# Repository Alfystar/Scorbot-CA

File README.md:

------------

# Scorbot-CA (Controlli Automatici)
Progetto inizialmente portato avanti nell'ambito del corso di Controlli Automatici tenuto a Tor-Vergata nell'anno 2019
- Sviluppato da studenti del 3° Ing. Informatica
- Corso tenuto dal Professor: Daniele Carnevale

I componenti del gruppo originario erano:
- Emanuele Alfano
- Davide Antonini
- Del Papa Nicolò
- Francesco Ferrò
- Ilaria Angeloni
- Alberto Menichelli

Il progetto è attualmente portato avanti da Emanuele Alfano con la licenza [GPLv3](LICENSE "GPLv3")
<p align="center">
  
  <br>  
  
</p>

## Download/Cloning Repository
Per poter avere i sorgenti sul proprio computer, basterà usare git da terminale per clonare il Repository sulla propria macchina: 
A questo punto, compiliamo i sorgenti e installiamoli dentro /usr/local/bin
```
sudo apt install git    # Per poter scaricare i sorgenti
cd ~/Documents          # Directory di salvataggio dei sorgenti
git clone https://github.com/Alfystar/Scorbot-CA.git
```
Per vedere i sorgenti e relative guide di Compilazione andare [Qui](SW_Source/README.md)

## Documentazione
Per la realizzazione della documentazione del software si è usata la versione Comunity di Visual Paradigm.
Le classi non sono state documentate tutte al massimo dettaglio, mettendo invece enfasi sull'interconnessione, i pattern e la gerarchia delle classi presente.
er i dettagli implementativi il codice

## ScoreBoard
La scheda di controllo dello Scorbot è pensata per essere un ponte tra la meccanica del robot, e il sistema di controllo integrato all'interno di un computer Linux.

Il manuale di questo sotto sistema è trovabile [qui](1_Doc/ScorBoard_v2-MANUAL.pdf "qui").

### Eagle Board
There are 2 version of the board.
Each one have his firmware and his library.
They are drawing using EAGLE 9.4.2 Educetional.
View this project on [CADLAB.io](https://cadlab.io/project/1649). 

#####  Board V1:
In questa prima versione si sono utilizzati dei ponti H L298, e per leggere gli ACS712.
La scheda soffriva di vari problemi di connessioni tra i pin in fase di progetto, le quali sono tutte risolvibili a mano.
La scheda possiede un firmware di controllo che parla al Rapsberry Py per mezzo di una comunicazione SPI. Di questa prima vesione è stata scritta una [presentazione del progetto](1_Doc/ProjectPresentation-V1.pdf) ai fini dell'esame.

#####  Board V2:
In questa seconda scheda il cambio più evidente è nel driver motori che adesso è diventato un VNH5019, il quale ha integrato dentro una misura di corrente già scalata e non necessita di letture esterne, di questa scheda è presente anche un [**Manuale**](1_Doc/ScorBoard_v2-MANUAL.pdf "qui")., che descrive nel dettaglio i vari punti del progetto.
<p align="center">
  <i>Top Face</i>
   
  <br>
   
  <i>Bottom Face</i>
</p>

#### UART Comunication Arduino <--> Linux:
La scheda comunica con un computer mediante collegamento UART, qui è stata sviluppata una libreria per la comunicazione con un processo Linux (testata su Mint e KDE NEON, in generale ubunto based)

# QT Gui
Per controllare il Robot in maniera intuitiva si è pensato di usare un interfaccia grafica scritta in QT5, la quale permette di controllare il robot sia direttamente che per mezzo di un PID
<p align="center">
  <i>Main Window</i>
    <br>
   
  <br>
    <i>Uart Select</i>
	  <br>
   
    <br>
    <i>Setting Board Window</i>
	  <br>
   
    <br>
    <i>Free Move Window</i>
	  <br>

</p>

Per graficare i dati ricevuti è stata usata la libreria [qcustomplot](https://www.qcustomplot.com/index.php/introduction)

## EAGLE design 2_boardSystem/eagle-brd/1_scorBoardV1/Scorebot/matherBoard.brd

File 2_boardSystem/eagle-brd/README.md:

# Eagle File directory

la prima versione (1_scorBoardV1) possiede i seguenti errori:
- Il transistor di abilitazione elettrico del relè per i motori, attualmente è cortocircuitato poichè non funzionava.
La probabile causa di questo problema è che il carico è messo a emettitoere e non a colettore, rendendo il circuito adatto a un PNP e non a un NPN(che è stato progettato e comprato), in una versione successiva è necessario invertire il carico (la bobbina) con il relè.

- La piedinatura usata nell'alimentatore è errata rispetto a quella effettivamente presente, oltre ad alcuni errori che mi avevano fatto connettere 12V a 3.3V, sembra che non sia sufficente prendere la corrente da uno solo per volta di questi fili.
In una prossima versione andrebbero collegati tutti tra di loro già nella board, collegare bene i pin sbagliati e aggiungere un led di segnalazione sul filo dei 5V sempre presenti, poichè l'alimentatore anche se ha il cavo di enable(quello verde) cortocircuitato a massa, se non è assorbito un minimo di corrente cmq non si accende.
In generare riprogettare questo connettore vendendo gli infiniti schemi online e vedendo anche i fili saldati attualmente, che hanno corretto l'errore, quindi devono essere riportati sulla scheda.

- In questa scheda i 3.3V che dovevano andare al rapsberry sono stati tagliati, perchè all'inizio causavano il reset della board. Si è scoperto poi che i 3.3V erano quasi a 0 poichè cortocircuitati con 12V (evidentemente l'alimentatote andava in protezione), nella scheda successiva si può provare a collegarli quindi.

- Il Vref esterno a meno che non si prenda da meno di 1.1V è meglio levarlo potendo usare quello stabilizzato interno all'arduino

- Il connettore del Rapsberry è necessario ruotarlo di 180°, per permettere una comoda connessione con lo stesso, ovviamente così facendo bisogna rifare la strip ruotando uno dei 2 estremi, in generale controllare prima di collegare che i pin siano connessi bene

- Sempre al connettore collegare tutte le masse, i 5V e i 3.3V, così da massimizzare la potenza trasmessa

- Se si continua ad usare l'attuale relè, è necessario correggere il package della libreria da me scritta che così comè si monta all'indietro rispetto al desiderato.

- Sulla serigrafia aggiungere i sensori di corrente a quale motore fanno riferimento, per futuri debugging ad occhio

- Facilitate bypass del traslatore di livello, per leggere o annullarne la presenza (mettere una fila di pin uno per pin), e in generale spostarlo o dal lato accessibile o fuori

- Modificare la serigrafia per mettere dritto e più leggibile i loghi

Grazie per l'attenzione

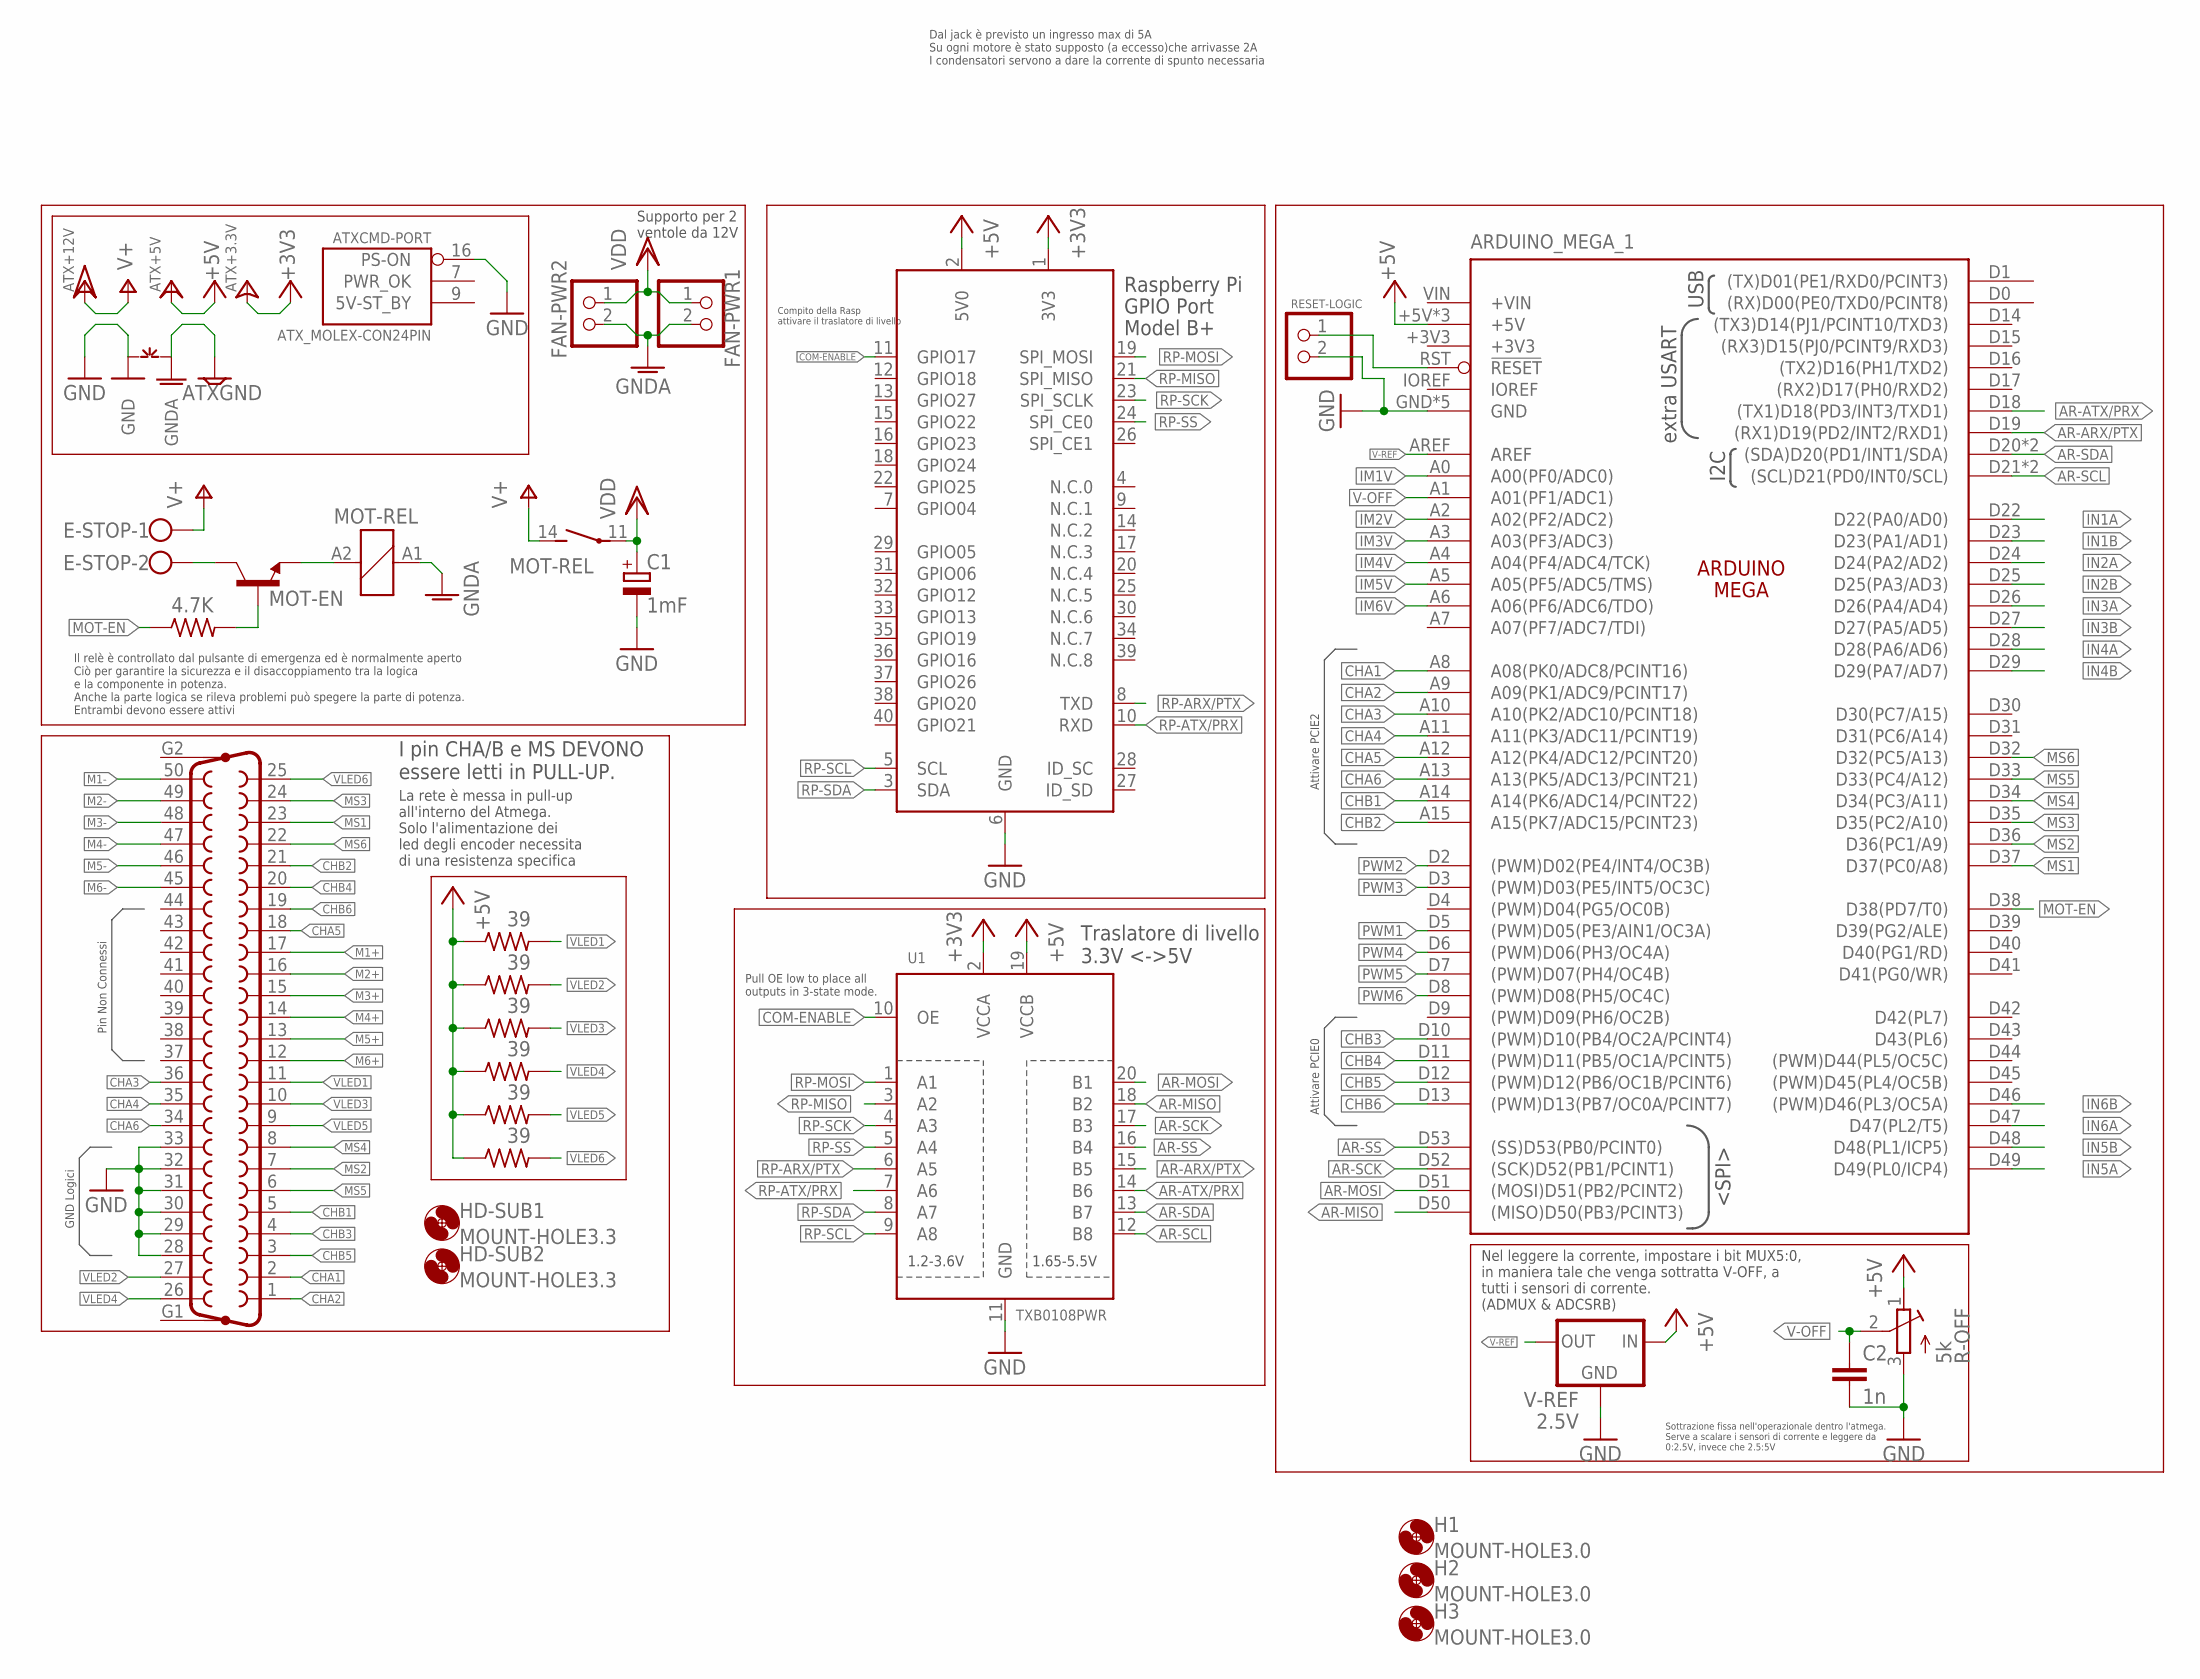
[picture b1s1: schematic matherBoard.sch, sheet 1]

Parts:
ARDUINO_MEGA_1: MEGA_ARDUINONO-HOLE; MEGA-NO-HOLE
ATX: ATX_MOLEX-CON24PIN; 5566-24
C1: 1mF; E5-13
C2: 1n; C025-024X044
D-SUB50: F50VP
E-STOP: W237-102
FAN-PWR1, FAN-PWR2: PINHD-1X2; 1X02
H1, H2, H3: MOUNT-HOLE3.0; 3,0
HD-SUB1, HD-SUB2: MOUNT-HOLE3.3; 3,3
MOT-EN: 2N5550-NPN-TO92-CBE; TO92-CBE
MOT-REL: RP530006; RP53
R1, R2, R3, R4, R5, R6: 39; 0204/5
R7: 4.7K; 0204/7
R-OFF: 5k; RTRIMT93YA
RASPBERRY-PY: RASPI_GPIO_B+_BOX
RESET-LOGIC: PINHD-1X2; 1X02
U1: TXB0108PWR; TSSOP20
V-REF: 2.5V; SOT23
~NUDEV~1: GND-GNDA1,27MM; GND-GNDA-1,27MM

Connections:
+3V3: ATX.1 (+3V3-ATX), ATX.2 (+3V3-ATX), ATX.12 (+3V3-ATX), ATX.13 (+3V3-ATX), RASPBERRY-PY.1 (3V3), U1.2 (VCCA)
+5V: ARDUINO_MEGA_1.+5V, ARDUINO_MEGA_1.+5V1 (+5V), ARDUINO_MEGA_1.+5V2 (+5V), ATX.4 (+5V-ATX), ATX.6 (+5V-ATX), ATX.21 (+5V-ATX), ATX.22 (+5V-ATX), ATX.23 (+5V-ATX), R1.1, R2.1, R3.1, R4.1, R5.1, R6.1, R-OFF.1 (E), RASPBERRY-PY.2 (5V0), U1.19 (VCCB), V-REF.3 (IN); also elsewhere on the board
AR-ARX/PTX: ARDUINO_MEGA_1.D19 ((RX1)D19(PD2/INT2/RXD1)), U1.15 (B5)
AR-ATX/PRX: ARDUINO_MEGA_1.D18 ((TX1)D18(PD3/INT3/TXD1)), U1.14 (B6)
AR-MISO: ARDUINO_MEGA_1.D50 ((MISO)D50(PB3/PCINT3)), U1.18 (B2)
AR-MOSI: ARDUINO_MEGA_1.D51 ((MOSI)D51(PB2/PCINT2)), U1.20 (B1)
AR-SCK: ARDUINO_MEGA_1.D52 ((SCK)D52(PB1/PCINT1)), U1.17 (B3)
AR-SCL: ARDUINO_MEGA_1.D21 ((SCL)D21(PD0/INT0/SCL)), ARDUINO_MEGA_1.SCL1 ((SCL)D21(PD0/INT0/SCL)), U1.12 (B8)
AR-SDA: ARDUINO_MEGA_1.D20 ((SDA)D20(PD1/INT1/SDA)), ARDUINO_MEGA_1.SDA1 ((SDA)D20(PD1/INT1/SDA)), U1.13 (B7)
AR-SS: ARDUINO_MEGA_1.D53 ((SS)D53(PB0/PCINT0)), U1.16 (B4)
CHA1: ARDUINO_MEGA_1.A8 (A08(PK0/ADC8/PCINT16)), D-SUB50.2
CHA2: ARDUINO_MEGA_1.A9 (A09(PK1/ADC9/PCINT17)), D-SUB50.1
CHA3: ARDUINO_MEGA_1.A10 (A10(PK2/ADC10/PCINT18)), D-SUB50.36
CHA4: ARDUINO_MEGA_1.A11 (A11(PK3/ADC11/PCINT19)), D-SUB50.35
CHA5: ARDUINO_MEGA_1.A12 (A12(PK4/ADC12/PCINT20)), D-SUB50.18
CHA6: ARDUINO_MEGA_1.A13 (A13(PK5/ADC13/PCINT21)), D-SUB50.34
CHB1: ARDUINO_MEGA_1.A14 (A14(PK6/ADC14/PCINT22)), D-SUB50.5
CHB2: ARDUINO_MEGA_1.A15 (A15(PK7/ADC15/PCINT23)), D-SUB50.21
CHB3: ARDUINO_MEGA_1.D10 ((PWM)D10(PB4/OC2A/PCINT4)), D-SUB50.4
CHB4: ARDUINO_MEGA_1.D11 ((PWM)D11(PB5/OC1A/PCINT5)), D-SUB50.20
CHB5: ARDUINO_MEGA_1.D12 ((PWM)D12(PB6/OC1B/PCINT6)), D-SUB50.3
CHB6: ARDUINO_MEGA_1.D13 ((PWM)D13(PB7/OC0A/PCINT7)), D-SUB50.19
COM-ENABLE: RASPBERRY-PY.11 (GPIO17), U1.10 (OE)
GND: ARDUINO_MEGA_1.GND, ARDUINO_MEGA_1.GND1 (GND), ARDUINO_MEGA_1.GND2 (GND), ARDUINO_MEGA_1.GND3 (GND), ARDUINO_MEGA_1.GND4 (GND), ATX.16 (PS-ON), C1.-, C2.2, D-SUB50.28, D-SUB50.29, D-SUB50.30, D-SUB50.31, D-SUB50.32, D-SUB50.33, R-OFF.3 (A), RASPBERRY-PY.6 (GND), RESET-LOGIC.2, U1.11 (GND), V-REF.1 (GND), ~NUDEV~1.GND; also elsewhere on the board
GNDA: ATX.3 (GND-ATX), ATX.5 (GND-ATX), ATX.8 (GND-ATX), ATX.15 (GND-ATX), ATX.17 (GND-ATX), ATX.18 (GND-ATX), ATX.19 (GND-ATX), ATX.24 (GND-ATX), FAN-PWR1.2, FAN-PWR2.2, MOT-REL.A1 (1), ~NUDEV~1.GNDA; also elsewhere on the board
IM1V: ARDUINO_MEGA_1.A0 (A00(PF0/ADC0)); also elsewhere on the board
IM2V: ARDUINO_MEGA_1.A2 (A02(PF2/ADC2)); also elsewhere on the board
IM3V: ARDUINO_MEGA_1.A3 (A03(PF3/ADC3)); also elsewhere on the board
IM4V: ARDUINO_MEGA_1.A4 (A04(PF4/ADC4/TCK)); also elsewhere on the board
IM5V: ARDUINO_MEGA_1.A5 (A05(PF5/ADC5/TMS)); also elsewhere on the board
IM6V: ARDUINO_MEGA_1.A6 (A06(PF6/ADC6/TDO)); also elsewhere on the board
IN1A: ARDUINO_MEGA_1.D22 (D22(PA0/AD0)); also elsewhere on the board
IN1B: ARDUINO_MEGA_1.D23 (D23(PA1/AD1)); also elsewhere on the board
IN2A: ARDUINO_MEGA_1.D24 (D24(PA2/AD2)); also elsewhere on the board
IN2B: ARDUINO_MEGA_1.D25 (D25(PA3/AD3)); also elsewhere on the board
IN3A: ARDUINO_MEGA_1.D26 (D26(PA4/AD4)); also elsewhere on the board
IN3B: ARDUINO_MEGA_1.D27 (D27(PA5/AD5)); also elsewhere on the board
IN4A: ARDUINO_MEGA_1.D28 (D28(PA6/AD6)); also elsewhere on the board
IN4B: ARDUINO_MEGA_1.D29 (D29(PA7/AD7)); also elsewhere on the board
IN5A: ARDUINO_MEGA_1.D49 (D49(PL0/ICP4)); also elsewhere on the board
IN5B: ARDUINO_MEGA_1.D48 (D48(PL1/ICP5)); also elsewhere on the board
IN6A: ARDUINO_MEGA_1.D47 (D47(PL2/T5)); also elsewhere on the board
IN6B: ARDUINO_MEGA_1.D46 ((PWM)D46(PL3/OC5A)); also elsewhere on the board
M1+: D-SUB50.17; also elsewhere on the board
M1-: D-SUB50.50; also elsewhere on the board
M2+: D-SUB50.16; also elsewhere on the board
M2-: D-SUB50.49; also elsewhere on the board
M3+: D-SUB50.15; also elsewhere on the board
M3-: D-SUB50.48; also elsewhere on the board
M4+: D-SUB50.14; also elsewhere on the board
M4-: D-SUB50.47; also elsewhere on the board
M5+: D-SUB50.13; also elsewhere on the board
M5-: D-SUB50.46; also elsewhere on the board
M6+: D-SUB50.12; also elsewhere on the board
M6-: D-SUB50.45; also elsewhere on the board
MOT-EN: ARDUINO_MEGA_1.D38 (D38(PD7/T0)), R7.1
MS1: ARDUINO_MEGA_1.D37 (D37(PC0/A8)), D-SUB50.23
MS2: ARDUINO_MEGA_1.D36 (D36(PC1/A9)), D-SUB50.7
MS3: ARDUINO_MEGA_1.D35 (D35(PC2/A10)), D-SUB50.24
MS4: ARDUINO_MEGA_1.D34 (D34(PC3/A11)), D-SUB50.8
MS5: ARDUINO_MEGA_1.D33 (D33(PC4/A12)), D-SUB50.6
MS6: ARDUINO_MEGA_1.D32 (D32(PC5/A13)), D-SUB50.22
unnamed: E-STOP.2, MOT-EN.C
unnamed: MOT-EN.B, R7.2
unnamed: MOT-EN.E, MOT-REL.A2 (2)
unnamed: ARDUINO_MEGA_1.RST (!RESET), RESET-LOGIC.1
PWM1: ARDUINO_MEGA_1.D5 ((PWM)D05(PE3/AIN1/OC3A)); also elsewhere on the board
PWM2: ARDUINO_MEGA_1.D2 ((PWM)D02(PE4/INT4/OC3B)); also elsewhere on the board
PWM3: ARDUINO_MEGA_1.D3 ((PWM)D03(PE5/INT5/OC3C)); also elsewhere on the board
PWM4: ARDUINO_MEGA_1.D6 ((PWM)D06(PH3/OC4A)); also elsewhere on the board
PWM5: ARDUINO_MEGA_1.D7 ((PWM)D07(PH4/OC4B)); also elsewhere on the board
PWM6: ARDUINO_MEGA_1.D8 ((PWM)D08(PH5/OC4C)); also elsewhere on the board
RP-ARX/PTX: RASPBERRY-PY.8 (TXD), U1.6 (A5)
RP-ATX/PRX: RASPBERRY-PY.10 (RXD), U1.7 (A6)
RP-MISO: RASPBERRY-PY.21 (SPI_MISO), U1.3 (A2)
RP-MOSI: RASPBERRY-PY.19 (SPI_MOSI), U1.1 (A1)
RP-SCK: RASPBERRY-PY.23 (SPI_SCLK), U1.4 (A3)
RP-SCL: RASPBERRY-PY.5 (SCL), U1.9 (A8)
RP-SDA: RASPBERRY-PY.3 (SDA), U1.8 (A7)
RP-SS: RASPBERRY-PY.24 (SPI_CE0), U1.5 (A4)
V+: ATX.10 (VCC/2), ATX.11 (VCC/2), E-STOP.1, MOT-REL.14 (S)
V-OFF: ARDUINO_MEGA_1.A1 (A01(PF1/ADC1)), C2.1, R-OFF.2 (S)
V-REF: ARDUINO_MEGA_1.AREF, V-REF.2 (OUT)
VDD: C1.+, FAN-PWR1.1, FAN-PWR2.1, MOT-REL.11; also elsewhere on the board
VLED1: D-SUB50.11, R1.2
VLED2: D-SUB50.27, R2.2
VLED3: D-SUB50.10, R3.2
VLED4: D-SUB50.26, R4.2
VLED5: D-SUB50.9, R5.2
VLED6: D-SUB50.25, R6.2

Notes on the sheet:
GND Logici
Dal jack è previsto un ingresso max di 5A Su ogni motore è stato supposto (a eccesso)che arrivasse 2A I condensatori servono a dare la corrente di spunto necessaria
Il relè è controllato dal pulsante di emergenza ed è normalmente aperto Ciò per garantire la sicurezza e il disaccoppiamento tra la logica e la componente in potenza. Anche la parte logica se rileva problemi può spegere la parte di potenza. Entrambi devono essere attivi
La rete è messa in pull-up all'interno del Atmega. Solo l'alimentazione dei led degli encoder necessita di una resistenza specifica
Pin Non Connessi
Pull OE low to place all outputs in 3-state mode.
Attivare PCIE2
Attivare PCIE0
I pin CHA/B e MS DEVONO essere letti in PULL-UP.
Sottrazione fissa nell'operazionale dentro l'atmega. Serve a scalare i sensori di corrente e leggere da 0:2.5V, invece che 2.5:5V
Nel leggere la corrente, impostare i bit MUX5:0, in maniera tale che venga sottratta V-OFF, a tutti i sensori di corrente. (ADMUX & ADCSRB)
Supporto per 2 ventole da 12V
Traslatore di livello 3.3V <->5V
Compito della Rasp attivare il traslatore di livello

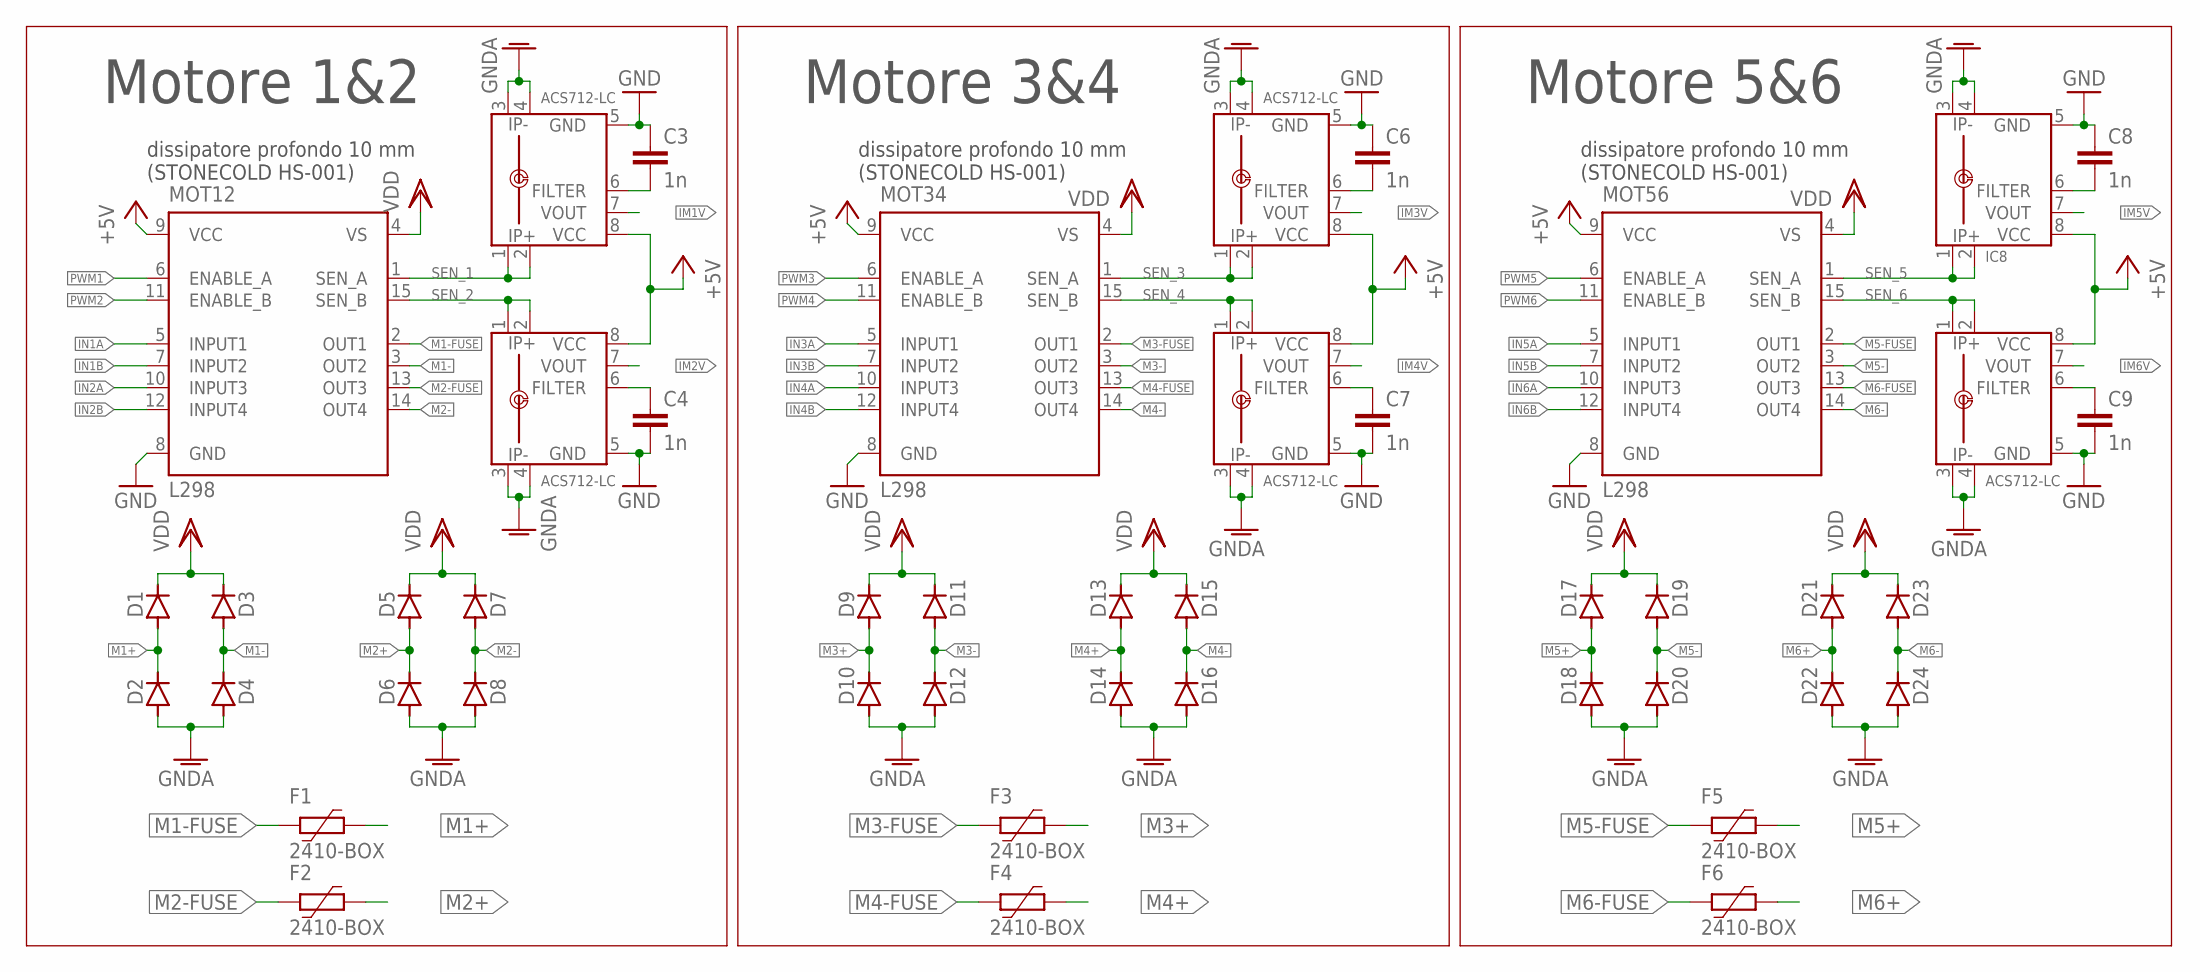
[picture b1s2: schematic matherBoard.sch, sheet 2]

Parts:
C3, C4, C6, C7, C8, C9: 1n; C025-024X044
D1, D2, D3, D4, D5, D6, D7, D8, D9, D10, D11, D12, D13, D14, D15, D16, D17, D18, D19, D20, D21, D22, D23, D24: ES2D; SMB
F1, F2, F3, F4, F5, F6: 2410-BOX; BELFUSE0679-3000-12
IC2, IC3, IC5, IC6, IC8, IC9: ACS712-LC; SOIC8
MOT12, MOT34, MOT56: L298; MULTIWATT-15

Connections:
+5V: IC2.8 (VCC), IC3.8 (VCC), IC5.8 (VCC), IC6.8 (VCC), IC8.8 (VCC), IC9.8 (VCC), MOT12.9 (VCC), MOT34.9 (VCC), MOT56.9 (VCC); also elsewhere on the board
GND: C3.1, C4.2, C6.1, C7.2, C8.1, C9.2, IC2.5 (GND), IC3.5 (GND), IC5.5 (GND), IC6.5 (GND), IC8.5 (GND), IC9.5 (GND), MOT12.8 (GND), MOT34.8 (GND), MOT56.8 (GND); also elsewhere on the board
GNDA: D2.A, D4.A, D6.A, D8.A, D10.A, D12.A, D14.A, D16.A, D18.A, D20.A, D22.A, D24.A, IC2.3 (IP-), IC2.4 (IP-1), IC3.3 (IP-), IC3.4 (IP-1), IC5.3 (IP-), IC5.4 (IP-1), IC6.3 (IP-), IC6.4 (IP-1), IC8.3 (IP-), IC8.4 (IP-1), IC9.3 (IP-), IC9.4 (IP-1); also elsewhere on the board
IM1V: IC2.7 (VOUT); also elsewhere on the board
IM2V: IC3.7 (VOUT); also elsewhere on the board
IM3V: IC5.7 (VOUT); also elsewhere on the board
IM4V: IC6.7 (VOUT); also elsewhere on the board
IM5V: IC8.7 (VOUT); also elsewhere on the board
IM6V: IC9.7 (VOUT); also elsewhere on the board
IN1A: MOT12.5 (INPUT1); also elsewhere on the board
IN1B: MOT12.7 (INPUT2); also elsewhere on the board
IN2A: MOT12.10 (INPUT3); also elsewhere on the board
IN2B: MOT12.12 (INPUT4); also elsewhere on the board
IN3A: MOT34.5 (INPUT1); also elsewhere on the board
IN3B: MOT34.7 (INPUT2); also elsewhere on the board
IN4A: MOT34.10 (INPUT3); also elsewhere on the board
IN4B: MOT34.12 (INPUT4); also elsewhere on the board
IN5A: MOT56.5 (INPUT1); also elsewhere on the board
IN5B: MOT56.7 (INPUT2); also elsewhere on the board
IN6A: MOT56.10 (INPUT3); also elsewhere on the board
IN6B: MOT56.12 (INPUT4); also elsewhere on the board
M1+: D1.A, D2.C, F1.1; also elsewhere on the board
M1-: D3.A, D4.C, MOT12.3 (OUT2); also elsewhere on the board
M1-FUSE: F1.2, MOT12.2 (OUT1)
M2+: D5.A, D6.C, F2.1; also elsewhere on the board
M2-: D7.A, D8.C, MOT12.14 (OUT4); also elsewhere on the board
M2-FUSE: F2.2, MOT12.13 (OUT3)
M3+: D9.A, D10.C, F3.1; also elsewhere on the board
M3-: D11.A, D12.C, MOT34.3 (OUT2); also elsewhere on the board
M3-FUSE: F3.2, MOT34.2 (OUT1)
M4+: D13.A, D14.C, F4.1; also elsewhere on the board
M4-: D15.A, D16.C, MOT34.14 (OUT4); also elsewhere on the board
M4-FUSE: F4.2, MOT34.13 (OUT3)
M5+: D17.A, D18.C, F5.1; also elsewhere on the board
M5-: D19.A, D20.C, MOT56.3 (OUT2); also elsewhere on the board
M5-FUSE: F5.2, MOT56.2 (OUT1)
M6+: D21.A, D22.C, F6.1; also elsewhere on the board
M6-: D23.A, D24.C, MOT56.14 (OUT4); also elsewhere on the board
M6-FUSE: F6.2, MOT56.13 (OUT3)
unnamed: C3.2, IC2.6 (FILTER)
unnamed: C4.1, IC3.6 (FILTER)
unnamed: C6.2, IC5.6 (FILTER)
unnamed: C7.1, IC6.6 (FILTER)
unnamed: C8.2, IC8.6 (FILTER)
unnamed: C9.1, IC9.6 (FILTER)
PWM1: MOT12.6 (ENABLE_A); also elsewhere on the board
PWM2: MOT12.11 (ENABLE_B); also elsewhere on the board
PWM3: MOT34.6 (ENABLE_A); also elsewhere on the board
PWM4: MOT34.11 (ENABLE_B); also elsewhere on the board
PWM5: MOT56.6 (ENABLE_A); also elsewhere on the board
PWM6: MOT56.11 (ENABLE_B); also elsewhere on the board
SEN_1: IC2.1 (IP+), IC2.2 (IP+1), MOT12.1 (SEN_A)
SEN_2: IC3.1 (IP+), IC3.2 (IP+1), MOT12.15 (SEN_B)
SEN_3: IC5.1 (IP+), IC5.2 (IP+1), MOT34.1 (SEN_A)
SEN_4: IC6.1 (IP+), IC6.2 (IP+1), MOT34.15 (SEN_B)
SEN_5: IC8.1 (IP+), IC8.2 (IP+1), MOT56.1 (SEN_A)
SEN_6: IC9.1 (IP+), IC9.2 (IP+1), MOT56.15 (SEN_B)
VDD: D1.C, D3.C, D5.C, D7.C, D9.C, D11.C, D13.C, D15.C, D17.C, D19.C, D21.C, D23.C, MOT12.4 (VS), MOT34.4 (VS), MOT56.4 (VS); also elsewhere on the board

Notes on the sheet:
dissipatore profondo 10 mm (STONECOLD HS-001)
Motore 1&2
Motore 3&4
Motore 5&6

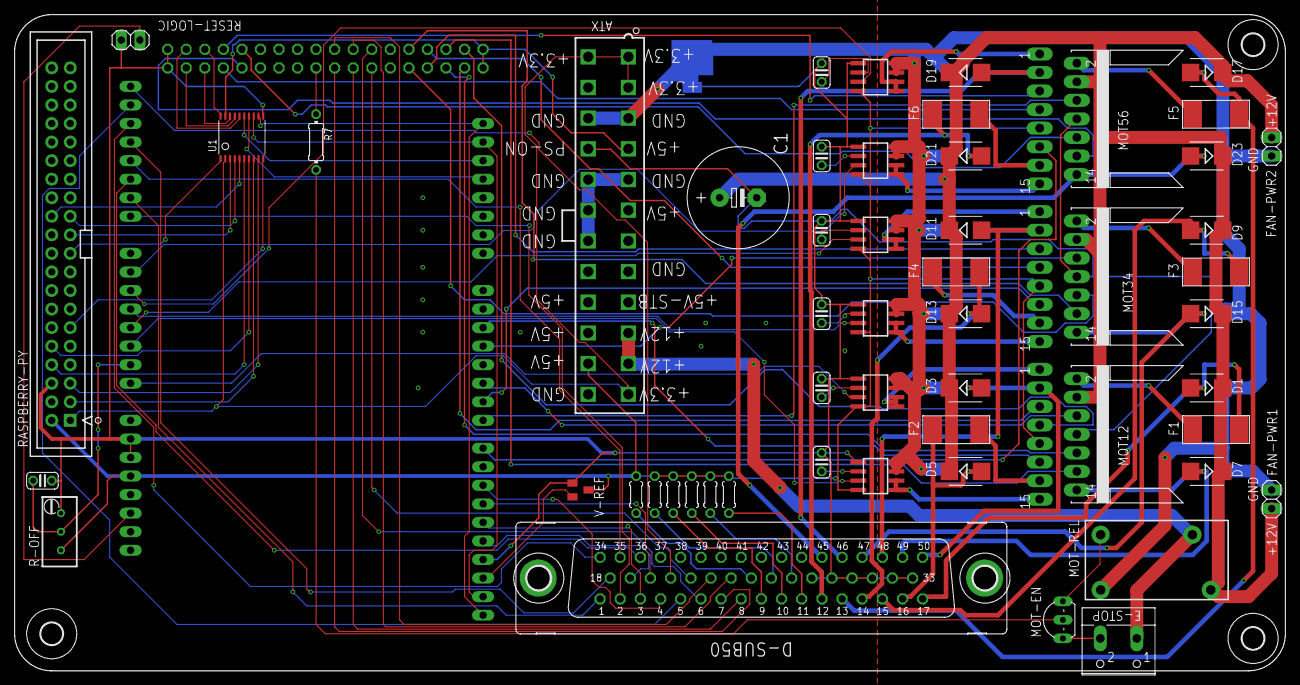
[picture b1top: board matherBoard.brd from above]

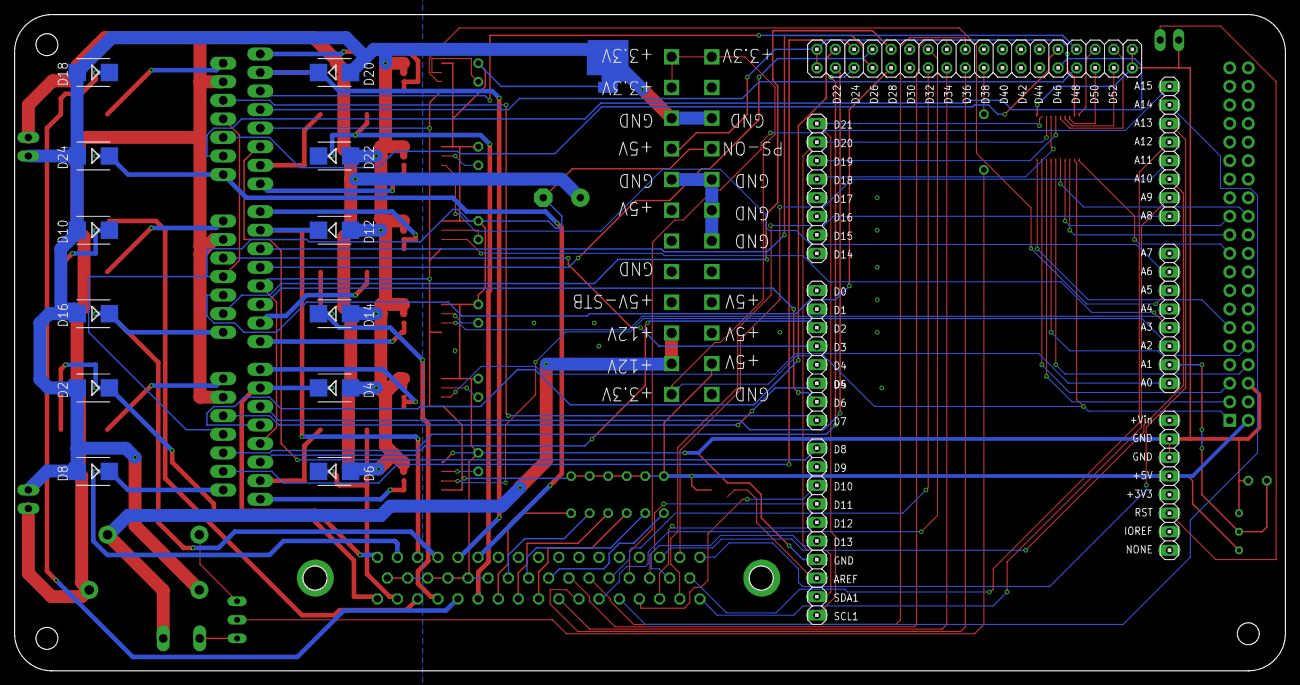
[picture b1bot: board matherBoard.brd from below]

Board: 2 copper layers, 174.0 x 89.8 mm, 73 parts (14 on the bottom side), 108 nets.

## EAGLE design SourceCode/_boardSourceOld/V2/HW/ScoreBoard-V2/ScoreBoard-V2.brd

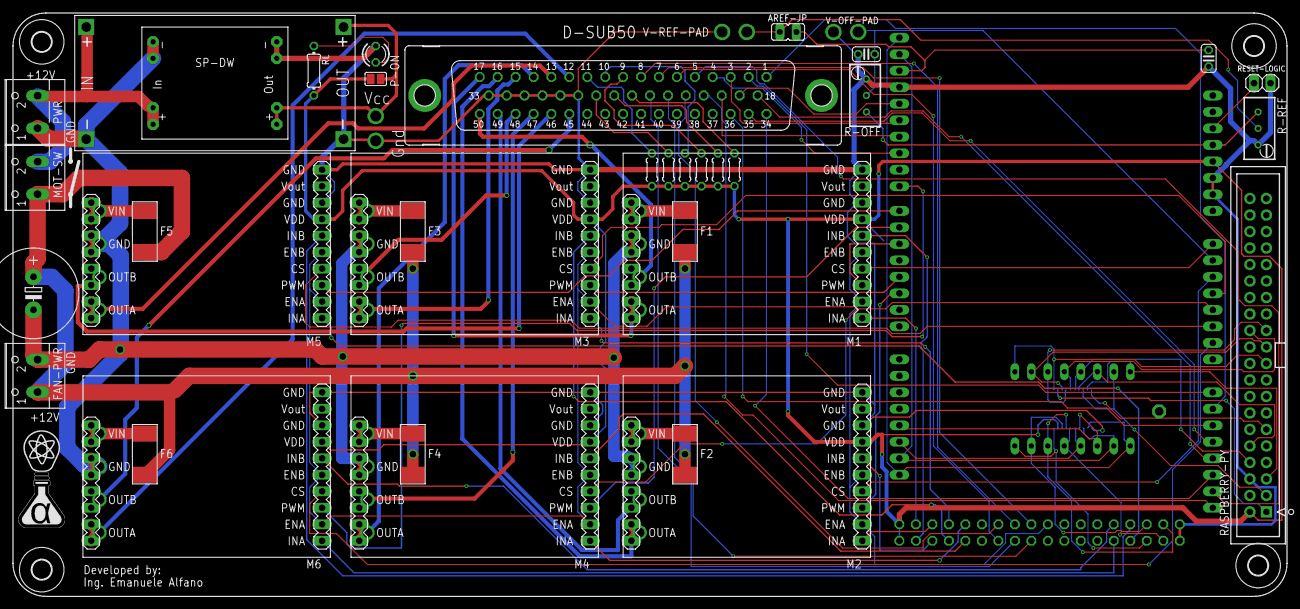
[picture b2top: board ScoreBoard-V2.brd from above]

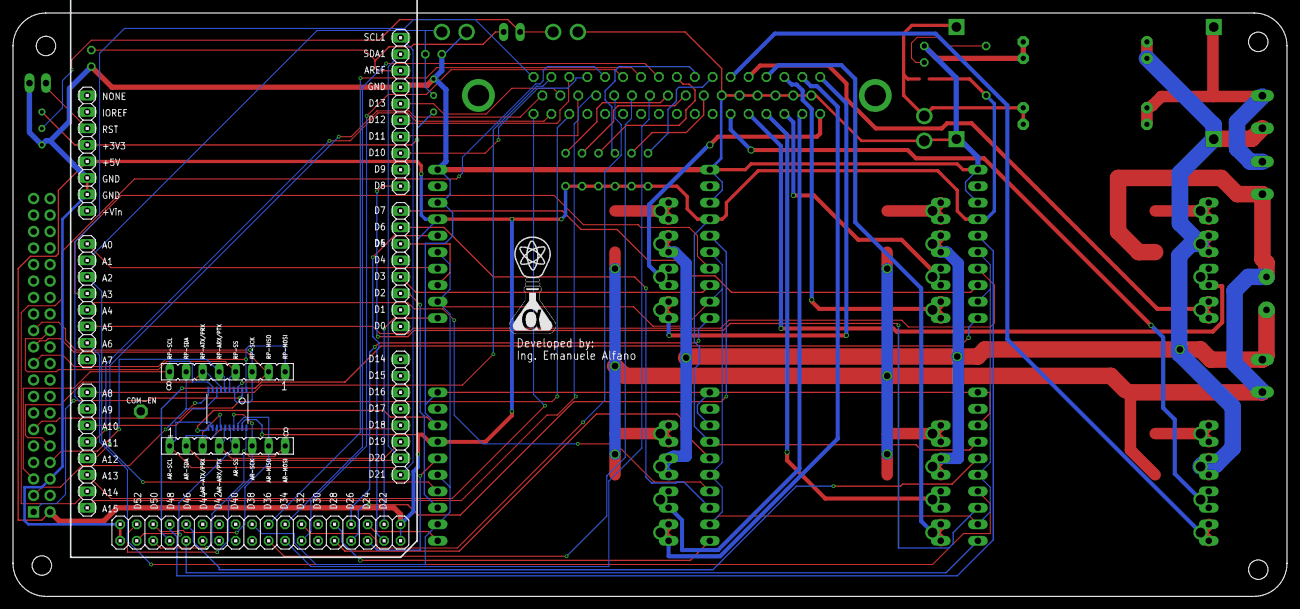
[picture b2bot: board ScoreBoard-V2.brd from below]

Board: 2 copper layers, 196.2 x 89.8 mm, 48 parts (5 on the bottom side), 97 nets.

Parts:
ARDUINO_MEGA_1: MEGA_ARDUINONO-HOLE; MEGA-NO-HOLE
AREF-JP: JP1
C1: 1mF; E5-13
C2, C3: 1n; C025-024X044
COM-EN: PTR1PAD1-13; P1-13
D-SUB50: F50VP
F1, F2, F3, F4, F5, F6: 2410-BOX; BELFUSE0679-3000-12
FAN-PWR: W237-102
H1, H2, H3, H4: MOUNT-HOLE3.0; 3,0
M1, M2, M3, M4, M5, M6: VNH5019
MOT-SW: W237-102
P-ON: LED3MM
PWR: W237-102
R1, R2, R3, R4, R5, R6: 39; 0204/5
R-OFF: 5k; RTRIMT93YA
R-REF: 5k; RTRIMT93YA
RASPBERRY-PY: RASPI_GPIO_B+_BOX
RESET-LOGIC: 1X02
RL: 330; 0204/7
SJ2: SJ
SP-DW: DC/DC-STEP-DOWNGLOB; DC/DC-STEP-DOWN-UNIVERSAL
SV1, SV2: FE08
U1: TXB0108; TSSOP20
U$2, U$3: ALFY_15MM
V-OFF-PAD: TP2P2-38-17; P2-38-17
V-REF-PAD: TP2P2-38-17; P2-38-17
VTEST-: TP2P2-38-17; P2-38-17

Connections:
3.3V-ARD: ARDUINO_MEGA_1.+3V3, R-OFF.1, R-REF.1
+3V3: RASPBERRY-PY.1, U1.2
+5V: ARDUINO_MEGA_1.+5V, ARDUINO_MEGA_1.+5V1, ARDUINO_MEGA_1.+5V2, M1.VDD, M2.VDD, M3.VDD, M4.VDD, M5.VDD, M6.VDD, R1.1, R2.1, R3.1, R4.1, R5.1, R6.1, RASPBERRY-PY.2, RL.2, SJ2.2, U1.19
AR-ARX/PTX: ARDUINO_MEGA_1.D19, SV2.4, U1.15
AR-ATX/PRX: ARDUINO_MEGA_1.D18, SV2.3, U1.14
AR-MISO: ARDUINO_MEGA_1.D50, SV2.7, U1.18
AR-MOSI: ARDUINO_MEGA_1.D51, SV2.8, U1.20
AR-SCK: ARDUINO_MEGA_1.D52, SV2.6, U1.17
AR-SCL: ARDUINO_MEGA_1.D21, ARDUINO_MEGA_1.SCL1, SV2.1, U1.12
AR-SDA: ARDUINO_MEGA_1.D20, ARDUINO_MEGA_1.SDA1, SV2.2, U1.13
AR-SS: ARDUINO_MEGA_1.D53, SV2.5, U1.16
CHA1: ARDUINO_MEGA_1.A8, D-SUB50.2
CHA2: ARDUINO_MEGA_1.A9, D-SUB50.1
CHA3: ARDUINO_MEGA_1.A10, D-SUB50.36
CHA4: ARDUINO_MEGA_1.A11, D-SUB50.35
CHA5: ARDUINO_MEGA_1.A12, D-SUB50.18
CHA6: ARDUINO_MEGA_1.A13, D-SUB50.34
CHB1: ARDUINO_MEGA_1.A14, D-SUB50.5
CHB2: ARDUINO_MEGA_1.A15, D-SUB50.21
CHB3: ARDUINO_MEGA_1.D10, D-SUB50.4
CHB4: ARDUINO_MEGA_1.D11, D-SUB50.20
CHB5: ARDUINO_MEGA_1.D12, D-SUB50.3
CHB6: ARDUINO_MEGA_1.D13, D-SUB50.19
COM-ENABLE: COM-EN.TP, RASPBERRY-PY.11, U1.10
GND: ARDUINO_MEGA_1.GND, ARDUINO_MEGA_1.GND1, ARDUINO_MEGA_1.GND2, ARDUINO_MEGA_1.GND3, ARDUINO_MEGA_1.GND4, C2.2, C3.2, D-SUB50.28, D-SUB50.29, D-SUB50.30, D-SUB50.31, D-SUB50.32, D-SUB50.33, M1.GND, M1.GND1, M2.GND, M2.GND1, M3.GND, M3.GND1, M4.GND, M4.GND1, M5.GND, M5.GND1, M6.GND, M6.GND1, P-ON.K, R-OFF.3, R-REF.3, RASPBERRY-PY.6, RESET-LOGIC.2, SP-DW.OUT-, SP-DW.OUT-1, SP-DW.OUT-2, U1.11, V-OFF-PAD.TP-2, V-REF-PAD.TP-2, VTEST-.TP-2
GNDA: C1.-, FAN-PWR.2, M1.GND-P1, M1.GND-P2, M1.GND-P3, M2.GND-P1, M2.GND-P2, M2.GND-P3, M3.GND-P1, M3.GND-P2, M3.GND-P3, M4.GND-P1, M4.GND-P2, M4.GND-P3, M5.GND-P1, M5.GND-P2, M5.GND-P3, M6.GND-P1, M6.GND-P2, M6.GND-P3, PWR.1, SP-DW.IN-, SP-DW.IN-1, SP-DW.IN-2
IM1V: ARDUINO_MEGA_1.A0, M1.CS
IM2V: ARDUINO_MEGA_1.A2, M2.CS
IM3V: ARDUINO_MEGA_1.A3, M3.CS
IM4V: ARDUINO_MEGA_1.A4, M4.CS
IM5V: ARDUINO_MEGA_1.A5, M5.CS
IM6V: ARDUINO_MEGA_1.A6, M6.CS
IN1A: ARDUINO_MEGA_1.D22, M1.INA
IN1B: ARDUINO_MEGA_1.D23, M1.INB
IN2A: ARDUINO_MEGA_1.D24, M2.INA
IN2B: ARDUINO_MEGA_1.D25, M2.INB
IN3A: ARDUINO_MEGA_1.D26, M3.INA
IN3B: ARDUINO_MEGA_1.D27, M3.INB
IN4A: ARDUINO_MEGA_1.D28, M4.INA
IN4B: ARDUINO_MEGA_1.D29, M4.INB
IN5A: ARDUINO_MEGA_1.D49, M5.INA
IN5B: ARDUINO_MEGA_1.D48, M5.INB
IN6A: ARDUINO_MEGA_1.D47, M6.INA
IN6B: ARDUINO_MEGA_1.D46, M6.INB
M1+: D-SUB50.17, M1.OUTA, M1.OUTA2, M1.OUTA3
M1-: D-SUB50.50, M1.OUTB, M1.OUTB1, M1.OUTB3
M1-FUSE: F1.1, M1.VIN0, M1.VIN1, M1.VIN2
M2+: D-SUB50.16, M2.OUTA, M2.OUTA2, M2.OUTA3
M2-: D-SUB50.49, M2.OUTB, M2.OUTB1, M2.OUTB3
M2-FUSE: F2.1, M2.VIN0, M2.VIN1, M2.VIN2
M3+: D-SUB50.15, M3.OUTA, M3.OUTA2, M3.OUTA3
M3-: D-SUB50.48, M3.OUTB, M3.OUTB1, M3.OUTB3
M3-FUSE: F3.1, M3.VIN0, M3.VIN1, M3.VIN2
M4+: D-SUB50.14, M4.OUTA, M4.OUTA2, M4.OUTA3
M4-: D-SUB50.47, M4.OUTB, M4.OUTB1, M4.OUTB3
M4-FUSE: F4.1, M4.VIN0, M4.VIN1, M4.VIN2
M5+: D-SUB50.13, M5.OUTA, M5.OUTA2, M5.OUTA3
M5-: D-SUB50.46, M5.OUTB, M5.OUTB1, M5.OUTB3
M5-FUSE: F5.1, M5.VIN0, M5.VIN1, M5.VIN2
M6+: D-SUB50.12, M6.OUTA, M6.OUTA2, M6.OUTA3
M6-: D-SUB50.45, M6.OUTB, M6.OUTB1, M6.OUTB3
M6-FUSE: F6.1, M6.VIN0, M6.VIN1, M6.VIN2
MOT-EN: ARDUINO_MEGA_1.D38, M1.ENA, M1.ENB, M2.ENA, M2.ENB, M3.ENA, M3.ENB, M4.ENA, M4.ENB, M5.ENA, M5.ENB, M6.ENA, M6.ENB
MS1: ARDUINO_MEGA_1.D37, D-SUB50.23
MS2: ARDUINO_MEGA_1.D36, D-SUB50.7
MS3: ARDUINO_MEGA_1.D35, D-SUB50.24
MS4: ARDUINO_MEGA_1.D34, D-SUB50.8
MS5: ARDUINO_MEGA_1.D33, D-SUB50.6
MS6: ARDUINO_MEGA_1.D32, D-SUB50.22
unnamed: P-ON.A, RL.1
unnamed: SJ2.1, SP-DW.OUT+, SP-DW.OUT+1, SP-DW.OUT+2, VTEST-.TP-1
unnamed: ARDUINO_MEGA_1.RST, RESET-LOGIC.1
PWM1: ARDUINO_MEGA_1.D5, M1.PWM
PWM2: ARDUINO_MEGA_1.D2, M2.PWM
PWM3: ARDUINO_MEGA_1.D3, M3.PWM
PWM4: ARDUINO_MEGA_1.D6, M4.PWM
PWM5: ARDUINO_MEGA_1.D7, M5.PWM
PWM6: ARDUINO_MEGA_1.D8, M6.PWM
RP-ARX/PTX: RASPBERRY-PY.8, SV1.5, U1.6
RP-ATX/PRX: RASPBERRY-PY.10, SV1.6, U1.7
RP-MISO: RASPBERRY-PY.21, SV1.2, U1.3
RP-MOSI: RASPBERRY-PY.19, SV1.1, U1.1
RP-SCK: RASPBERRY-PY.23, SV1.3, U1.4
RP-SCL: RASPBERRY-PY.5, SV1.8, U1.9
RP-SDA: RASPBERRY-PY.3, SV1.7, U1.8
RP-SS: RASPBERRY-PY.24, SV1.4, U1.5
V+: MOT-SW.2, PWR.2, SP-DW.IN+, SP-DW.IN+1, SP-DW.IN+2
V-OFF: ARDUINO_MEGA_1.A1, C3.1, R-OFF.2, V-OFF-PAD.TP-1
V-REF: ARDUINO_MEGA_1.AREF, AREF-JP.1, C2.1
V-REF-TRIMM: AREF-JP.2, R-REF.2, V-REF-PAD.TP-1
VDD: C1.+, F1.2, F2.2, F3.2, F4.2, F5.2, F6.2, FAN-PWR.1, MOT-SW.1
VLED1: D-SUB50.11, R1.2
VLED2: D-SUB50.27, R2.2
VLED3: D-SUB50.10, R3.2
VLED4: D-SUB50.26, R4.2
VLED5: D-SUB50.9, R5.2
VLED6: D-SUB50.25, R6.2

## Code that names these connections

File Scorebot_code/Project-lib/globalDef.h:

/*
 * pinDef.h
 *
 *  Created on: 22 mar 2019
 *      Author: alfy
 */

#ifndef PROJECT_LIB_GLOBALDEF_H_
#define PROJECT_LIB_GLOBALDEF_H_

#define motEn 38 //PD7

//define SPI
#define MISO 50
#define MOSI 51
#define SS 53
#define SCK 52

//define MOTORI
#define nMot 6
enum motCode {cMot1=0, cMot2, cMot3, cMot4, cMot5, cMot6};

#define EN1 5		//PE3
#define IN1A 22		//PA0
#define IN1B 23		//PA1

#define EN2 2		//PE4
#define IN2A 24		//PA2
#define IN2B 25		//PA3

#define EN3 3		//PE5
#define IN3A 26		//PA4
#define IN3B 27		//PA5

#define EN4 6		//PH3
#define IN4A 28		//PA6
#define IN4B 29		//PA7

#define EN5 7		//PH4
#define IN5A 49		//PL0
#define IN5B 48		//PL1

#define EN6 8		//PH5
#define IN6A 47		//PL2
#define IN6B 46		//PL3


typedef struct settingsBoard_ {
	int maxEn[nMot]; 		//valore massimo di passi prima di considerarsi fuori range di sicurezza (numeri pos)
	int minEn[nMot]; 		//valore minimo di passi prima di considerarsi fuori range di sicurezza (numeri neg)
	int maxCurrMed[nMot];	//valore massimo di corrente Efficace (con una media di 1 ms ~ ultime 8 letture), numero * 8 per semplificare i conti)
} settingsBoard;

extern settingsBoard sets;

#endif /* PROJECT_LIB_GLOBALDEF_H_ */

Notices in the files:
parts and their libraries:
diy-modules: Released under the Creative Commons Attribution 4.0 International License: http://creativecommons.org/licenses/by/4.0
